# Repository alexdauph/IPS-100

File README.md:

# IPS-100
Répertoire du code source, des fichiers de production et des exemples d'utilisation du module IPS-100

* [Librairies précompilées](https://github.com/alexdauph/IPS-100/tree/main/librairies)
* [Code source](https://github.com/alexdauph/IPS-100/tree/main/source)
* [Fichiers de production](https://github.com/alexdauph/IPS-100/tree/main/board/v3.0)
* [Vidéos](https://www.youtube.com/playlist?list=PLYlZ43pC6QAuAs4NA6EbOarvavoVzW4GN)

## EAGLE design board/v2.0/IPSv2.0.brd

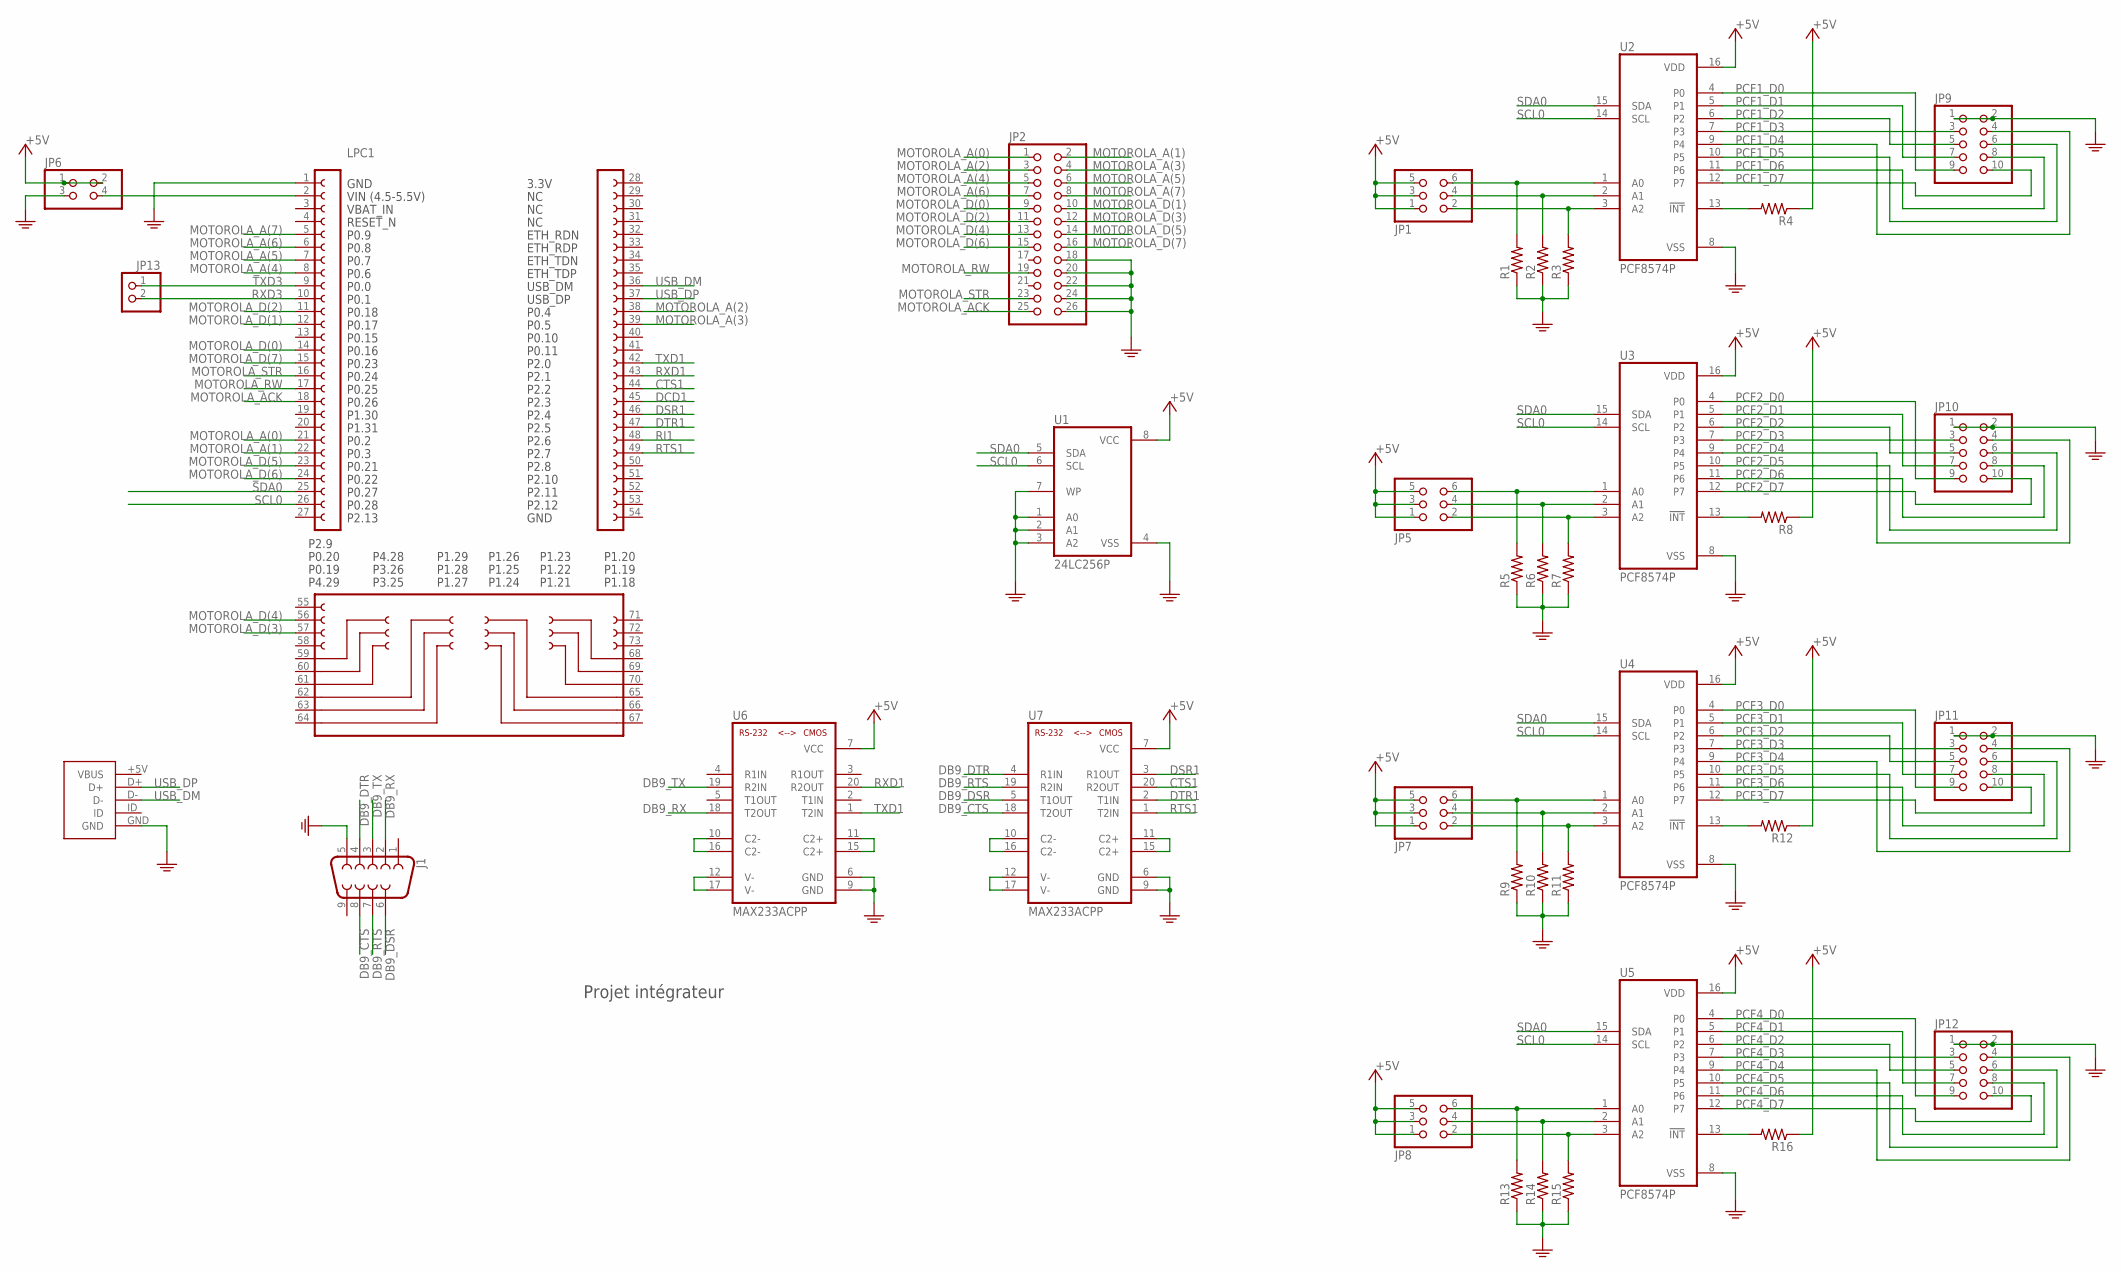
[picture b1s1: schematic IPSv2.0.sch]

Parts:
J1: DB9FEMALE; DB9
JP1, JP5, JP7, JP8: PINHD-2X3; 2X03
JP2: PINHD-2X13; 2X13
JP6: PINHD-2X2; 2X02
JP9, JP10, JP11, JP12: PINHD-2X5; 2X05
JP13: PINHD-1X2; 1X02
LPC1: LPCXPRESSO_LPC1769
R1, R2, R3, R4, R5, R6, R7, R8, R9, R10, R11, R12, R13, R14, R15, R16: R-US_M1206; M1206
U1: 24LC256P; DIP08
U2, U3, U4, U5: PCF8574P; DIP16
U6, U7: MAX233ACPP; DIP20
U$2: USB-MICRO-BREAKOUT

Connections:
+5V: JP1.1, JP1.3, JP1.5, JP5.1, JP5.3, JP5.5, JP6.1, JP6.2, JP7.1, JP7.3, JP7.5, JP8.1, JP8.3, JP8.5, R4.1, R8.1, R12.1, R16.1, U1.8 (VCC), U2.16 (VDD), U3.16 (VDD), U4.16 (VDD), U5.16 (VDD), U6.7 (VCC), U7.7 (VCC)
CTS1: LPC1.44, U7.20 (R2OUT)
DB9_CTS: J1.8, U7.18 (T2OUT)
DB9_DSR: J1.6, U7.5 (T1OUT)
DB9_DTR: J1.4, U7.4 (R1IN)
DB9_RTS: J1.7, U7.19 (R2IN)
DB9_RX: J1.2, U6.18 (T2OUT)
DB9_TX: J1.3, U6.19 (R2IN)
DCD1: LPC1.45
DSR1: LPC1.46, U7.3 (R1OUT)
DTR1: LPC1.47, U7.2 (T1IN)
GND: J1.5, JP2.18, JP2.20, JP2.22, JP2.24, JP2.26, JP6.3, JP9.1, JP9.2, JP10.1, JP10.2, JP11.1, JP11.2, JP12.1, JP12.2, LPC1.1, R1.1, R2.1, R3.1, R5.1, R6.1, R7.1, R9.1, R10.1, R11.1, R13.1, R14.1, R15.1, U1.1 (A0), U1.2 (A1), U1.3 (A2), U1.4 (VSS), U1.7 (WP), U2.8 (VSS), U3.8 (VSS), U4.8 (VSS), U5.8 (VSS), U6.6 (GND), U6.9 (GND), U7.6 (GND), U7.9 (GND), U$2.GND
MOTOROLA_A(0): JP2.1, LPC1.21
MOTOROLA_A(1): JP2.2, LPC1.22
MOTOROLA_A(2): JP2.3, LPC1.38
MOTOROLA_A(3): JP2.4, LPC1.39
MOTOROLA_A(4): JP2.5, LPC1.8
MOTOROLA_A(5): JP2.6, LPC1.7
MOTOROLA_A(6): JP2.7, LPC1.6
MOTOROLA_A(7): JP2.8, LPC1.5
MOTOROLA_ACK: JP2.25, LPC1.18
MOTOROLA_D(0): JP2.9, LPC1.14
MOTOROLA_D(1): JP2.10, LPC1.12
MOTOROLA_D(2): JP2.11, LPC1.11
MOTOROLA_D(3): JP2.12, LPC1.57
MOTOROLA_D(4): JP2.13, LPC1.56
MOTOROLA_D(5): JP2.14, LPC1.23
MOTOROLA_D(6): JP2.15, LPC1.24
MOTOROLA_D(7): JP2.16, LPC1.15
MOTOROLA_RW: JP2.19, LPC1.17
MOTOROLA_STR: JP2.23, LPC1.16
unnamed: R8.2, U3.13 (!INT)
unnamed: U7.12 (V-), U7.17 (V-)
unnamed: R12.2, U4.13 (!INT)
unnamed: R4.2, U2.13 (!INT)
unnamed: U7.10 (C2-), U7.16 (C2-)
unnamed: U7.11 (C2+), U7.15 (C2+)
unnamed: JP6.4, LPC1.2
unnamed: R16.2, U5.13 (!INT)
unnamed: U6.12 (V-), U6.17 (V-)
unnamed: U6.10 (C2-), U6.16 (C2-)
unnamed: U6.11 (C2+), U6.15 (C2+)
PCF1_A0: JP1.6, R1.2, U2.1 (A0)
PCF1_A1: JP1.4, R2.2, U2.2 (A1)
PCF1_A2: JP1.2, R3.2, U2.3 (A2)
PCF1_D0: JP9.9, U2.4 (P0)
PCF1_D1: JP9.7, U2.5 (P1)
PCF1_D2: JP9.5, U2.6 (P2)
PCF1_D3: JP9.3, U2.7 (P3)
PCF1_D4: JP9.4, U2.9 (P4)
PCF1_D5: JP9.6, U2.10 (P5)
PCF1_D6: JP9.8, U2.11 (P6)
PCF1_D7: JP9.10, U2.12 (P7)
PCF2_A0: JP5.6, R5.2, U3.1 (A0)
PCF2_A1: JP5.4, R6.2, U3.2 (A1)
PCF2_A2: JP5.2, R7.2, U3.3 (A2)
PCF2_D0: JP10.9, U3.4 (P0)
PCF2_D1: JP10.7, U3.5 (P1)
PCF2_D2: JP10.5, U3.6 (P2)
PCF2_D3: JP10.3, U3.7 (P3)
PCF2_D4: JP10.4, U3.9 (P4)
PCF2_D5: JP10.6, U3.10 (P5)
PCF2_D6: JP10.8, U3.11 (P6)
PCF2_D7: JP10.10, U3.12 (P7)
PCF3_A0: JP7.6, R9.2, U4.1 (A0)
PCF3_A1: JP7.4, R10.2, U4.2 (A1)
PCF3_A2: JP7.2, R11.2, U4.3 (A2)
PCF3_D0: JP11.9, U4.4 (P0)
PCF3_D1: JP11.7, U4.5 (P1)
PCF3_D2: JP11.5, U4.6 (P2)
PCF3_D3: JP11.3, U4.7 (P3)
PCF3_D4: JP11.4, U4.9 (P4)
PCF3_D5: JP11.6, U4.10 (P5)
PCF3_D6: JP11.8, U4.11 (P6)
PCF3_D7: JP11.10, U4.12 (P7)
PCF4_A0: JP8.6, R13.2, U5.1 (A0)
PCF4_A1: JP8.4, R14.2, U5.2 (A1)
PCF4_A2: JP8.2, R15.2, U5.3 (A2)
PCF4_D0: JP12.9, U5.4 (P0)
PCF4_D1: JP12.7, U5.5 (P1)
PCF4_D2: JP12.5, U5.6 (P2)
PCF4_D3: JP12.3, U5.7 (P3)
PCF4_D4: JP12.4, U5.9 (P4)
PCF4_D5: JP12.6, U5.10 (P5)
PCF4_D6: JP12.8, U5.11 (P6)
PCF4_D7: JP12.10, U5.12 (P7)
RI1: LPC1.48
RTS1: LPC1.49, U7.1 (T2IN)
RXD1: LPC1.43, U6.20 (R2OUT)
RXD3: JP13.2, LPC1.10
SCL0: LPC1.26, U1.6 (SCL), U2.14 (SCL), U3.14 (SCL), U4.14 (SCL), U5.14 (SCL)
SDA0: LPC1.25, U1.5 (SDA), U2.15 (SDA), U3.15 (SDA), U4.15 (SDA), U5.15 (SDA)
TXD1: LPC1.42, U6.1 (T2IN)
TXD3: JP13.1, LPC1.9
USB_DM: LPC1.36, U$2.D-
USB_DP: LPC1.37, U$2.D+
VBUS: U$2.+5V (VBUS)

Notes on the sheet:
Projet intégrateur

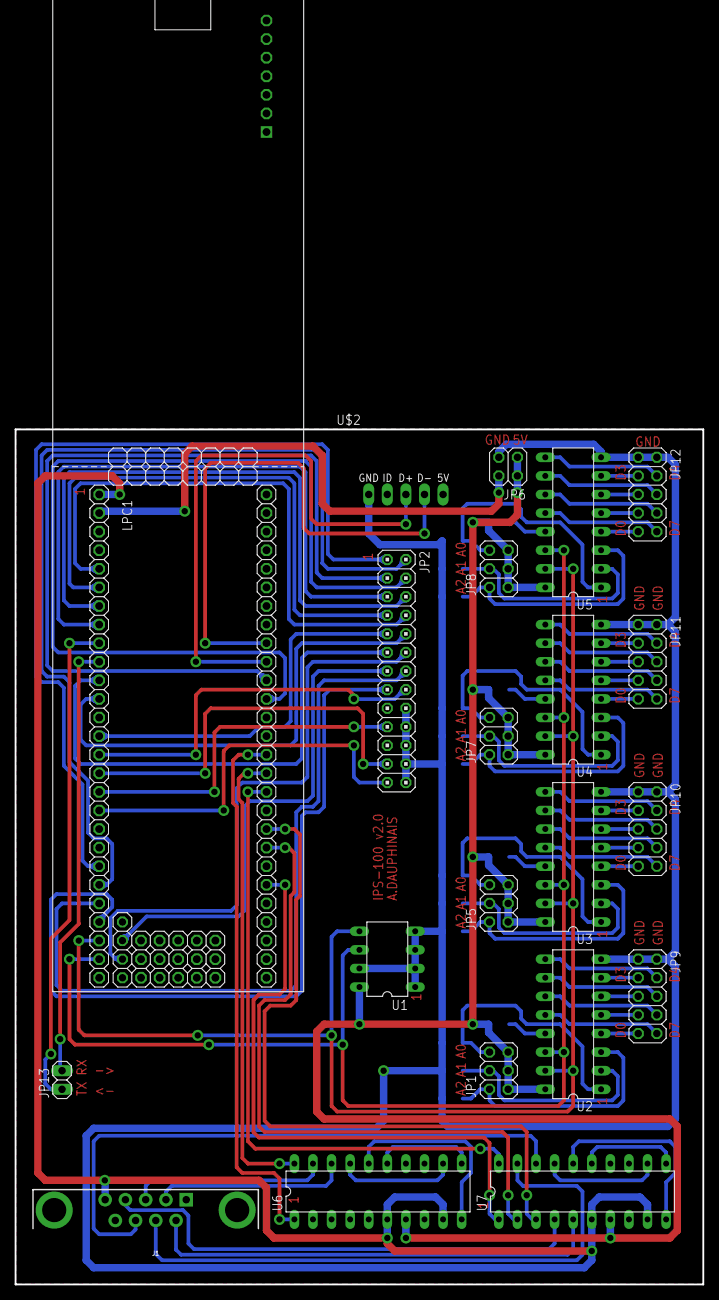
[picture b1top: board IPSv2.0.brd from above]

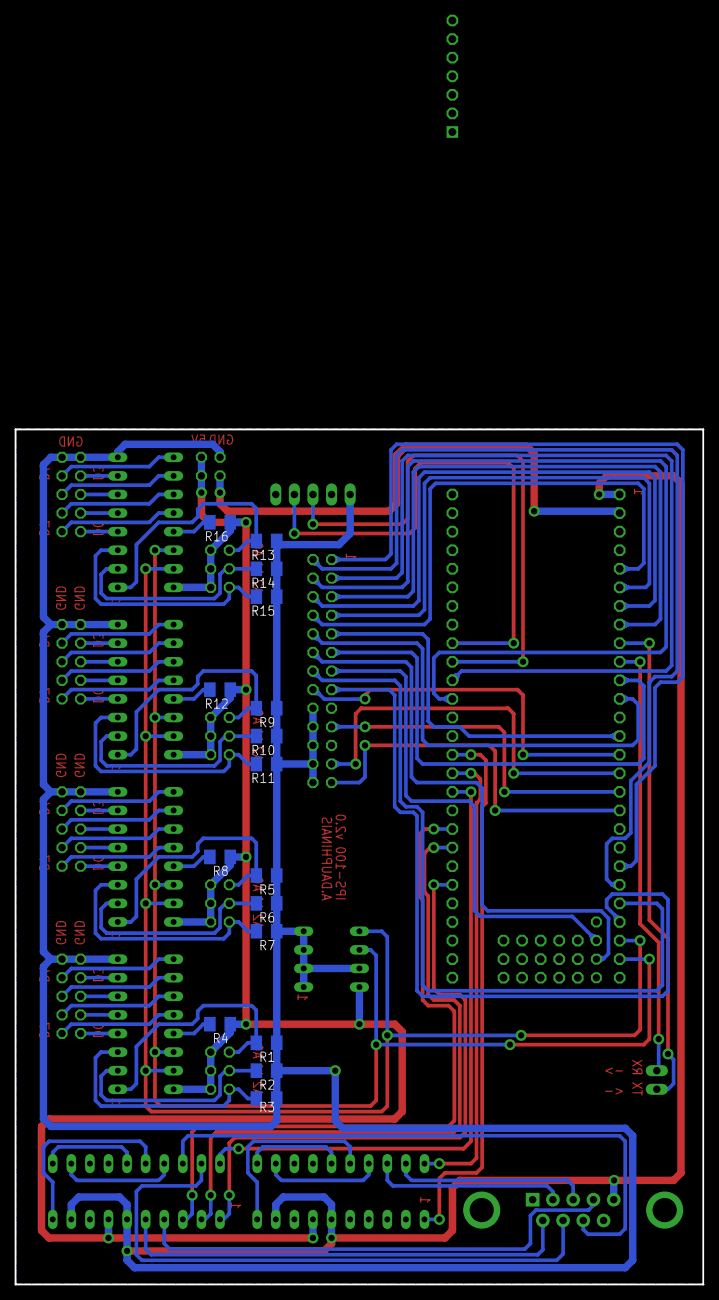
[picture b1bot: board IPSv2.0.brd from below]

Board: 2 copper layers, 94.0 x 116.8 mm, 37 parts (16 on the bottom side), 94 nets.

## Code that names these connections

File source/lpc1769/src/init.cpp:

#include "vcom.h"

//#include "IPS-100.h"
#include "codes.h"
#include "pinFunctions.h"
#include "macros.h"
#include "timers.h"
#include "I2C.h"
#include "GPIO.h"
#include "clock.h"
#include "UART.h"
#include "interrupt.h"
#include "DMA.h"


void VCOM::ST_init() {
	SB(STCTRL,2);
	ST_TIMEOUT(10);
}

void VCOM::i2c_init() {
	SB(PCONP, 7);
	I2B(PCLKSEL0,14,1);				//24MHz

	I2B(PINSEL1, 22, 1);			//SDA0
	I2B(PINSEL1, 24, 1);			//SCL0
	I2B(PINMODE1, 22, 2);			//Float
	I2B(PINMODE1, 24, 2);			//Float
	I2CPADCFG = 0;					//Standard drive mode

	I2C0SCLL = 480;					//100KHz 50%
	I2C0SCLH = 480;					//100KHz 50%

	I2C0CONCLR = 0x7F;				//Clear CTRL register
	I2C0CONSET = 0x40;				//I2C Enable
}

void VCOM::uart1_init() {
	SB(PCONP, 4);				//Enable PCLK
	U1TER = 0;					//Disable TX while configuration

	I2B(PCLKSEL0,18,0);			//24MHz
	U1LCR = 0x83;				//DLAB=1 to set baud rate
	U1DLM = 0;					//24MHz/115200/16
	U1DLL = 0x0D;
	U1FDR = 0x10;
	U1LCR = 0x03;				//DLAB = 0
	U1MCR = 0x00;

	I2B(PINSEL4,0,2);			//TXD1 P2.0 OUT
	I2B(PINSEL4,2,2);			//RXD1 P2.1	IN
	I2B(PINSEL4,4,2);			//CTS1 P2.2	IN
	I2B(PINSEL4,6,2);			//DCD1 P2.3 IN
	I2B(PINSEL4,8,2);			//DSR1 P2.4 IN
	I2B(PINSEL4,10,2);			//DTR1 P2.5 OUT
	I2B(PINSEL4,12,2);			//RI1  P2.6	IN
	I2B(PINSEL4,14,2);			//RTS1 P2.7	OUT

	I2B(PINMODE4,0,2);			//TXD1 Float
	I2B(PINMODE4,2,2);			//RXD1 Float
	I2B(PINMODE4,4,2);			//CTS1 Float
	I2B(PINMODE4,6,2);			//DCD1 Float
	I2B(PINMODE4,8,2);			//DSR1 Float
	I2B(PINMODE4,10,2);			//DTR1 Float
	I2B(PINMODE4,12,2);			//RI1  Float
	I2B(PINMODE4,14,2);			//DCD1 Float

	U1FCR = 0xC7;
	SB(U1TER, 7);
	while (VB(U1LSR, 0)) { U1RBR; }

	SB(U1IER, 0);				//Enable RX interrupt
	SB(ISER0, 6);				//Enable UART3 interrupt
}

void VCOM::uart3_init() {
	SB(PCONP, 25);				//Enable PCLK
	U3TER = 0;					//Disable TX while configuration

	I2B(PCLKSEL1,18,0);			//24MHz
	U3LCR = 0x83;				//DLAB=1 to set baud rate
	U3DLM = 0;					//24MHz/115200/16
	U3DLL = 0x0D;
	U3FDR = 0x10;
	U3LCR = 0x03;				//DLAB = 0

	I2B(PINSEL0,0,2);			//TXD3 P0.0
	I2B(PINSEL0,2,2);			//RXD3 P0.1
	I2B(PINMODE0,0,2);			//TXD3 Float
	I2B(PINMODE0,2,2);			//RXD3 Float

	U3FCR = 0x87;				//TODO put 0xC7
	SB(U3TER, 7);
	while (VB(U3LSR, 0)) { U3RBR; }

	SB(U3IER, 0);				//Enable RX interrupt
	SB(ISER0,8);				//Enable UART3 interrupt
}

void VCOM::motorola_init() {
	PINSEL0 &= 0xFFF0000F;		//GPIO ADD
	PINSEL1 &= 0xFFC00000;		//GPIO DATA / STR / RW / ACK

	PINMODE0 |= 0x000FFFF0;		//PULL-DOWN ADD
	PINMODE1 |= 0x0000FFFF;		//PULL-DOWN DATA
	PINMODE1 &= 0xFFC0FFFF;		//PULL-UP STR / RW / ACK

	FIO0DIR |= 0x03FF03FC;		//OUTPUT ADD / DATA

	FIO0PIN |= 0x03000000;

	I2B(PINSEL4, 20, 1);		//INTERRUPT sur EINT0
	I2B(PINMODE4, 20, 3);		//PULL-UP

	//ADD	pull-down	output		GPIO 0.2 - 0.9
	//DATA	pull-down	I/0			GPIO 0.16 - 0.23

	//STR 	pull-up		input		GPIO 0.24
	//RW 	pull-up 	input		GPIO 0.25
	//ACK	pull-up?	output		GPIO 0.26
}

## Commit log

2020-10-02 First commit test
2020-10-02 Another commit
2020-10-02 Changing .gitignore
2020-10-02 Fresh empty project
2020-10-02 Added IPS files for Visual Studio
2020-10-02 Added all board files
2020-10-02 Edited readme.md
2020-10-02 Uploaded almost everything
2020-10-20 Added release mode and binaries
2020-10-20 Added debug/release for Visual Studio
2020-10-20 Removed *.launch
2020-10-20 Uploaded project
2020-11-02 Added Release and Debug for Visual Studio library
2020-11-02 Fixed untracked files
2020-11-02 Added untracked files
2020-11-02 Standardized method names
2021-01-18 Added exerciseur source code
2021-01-18 Added Debug/Release folders
2021-01-18 Edited exerciseur

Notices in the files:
parts and their libraries:
00_Actifs: Copyright ©Raymond Paquin 2001
00_Connectors: Licensing: Creative Commons ShareAlike 4.0 International - https://creativecommons.org/licenses/by-sa/4.0
